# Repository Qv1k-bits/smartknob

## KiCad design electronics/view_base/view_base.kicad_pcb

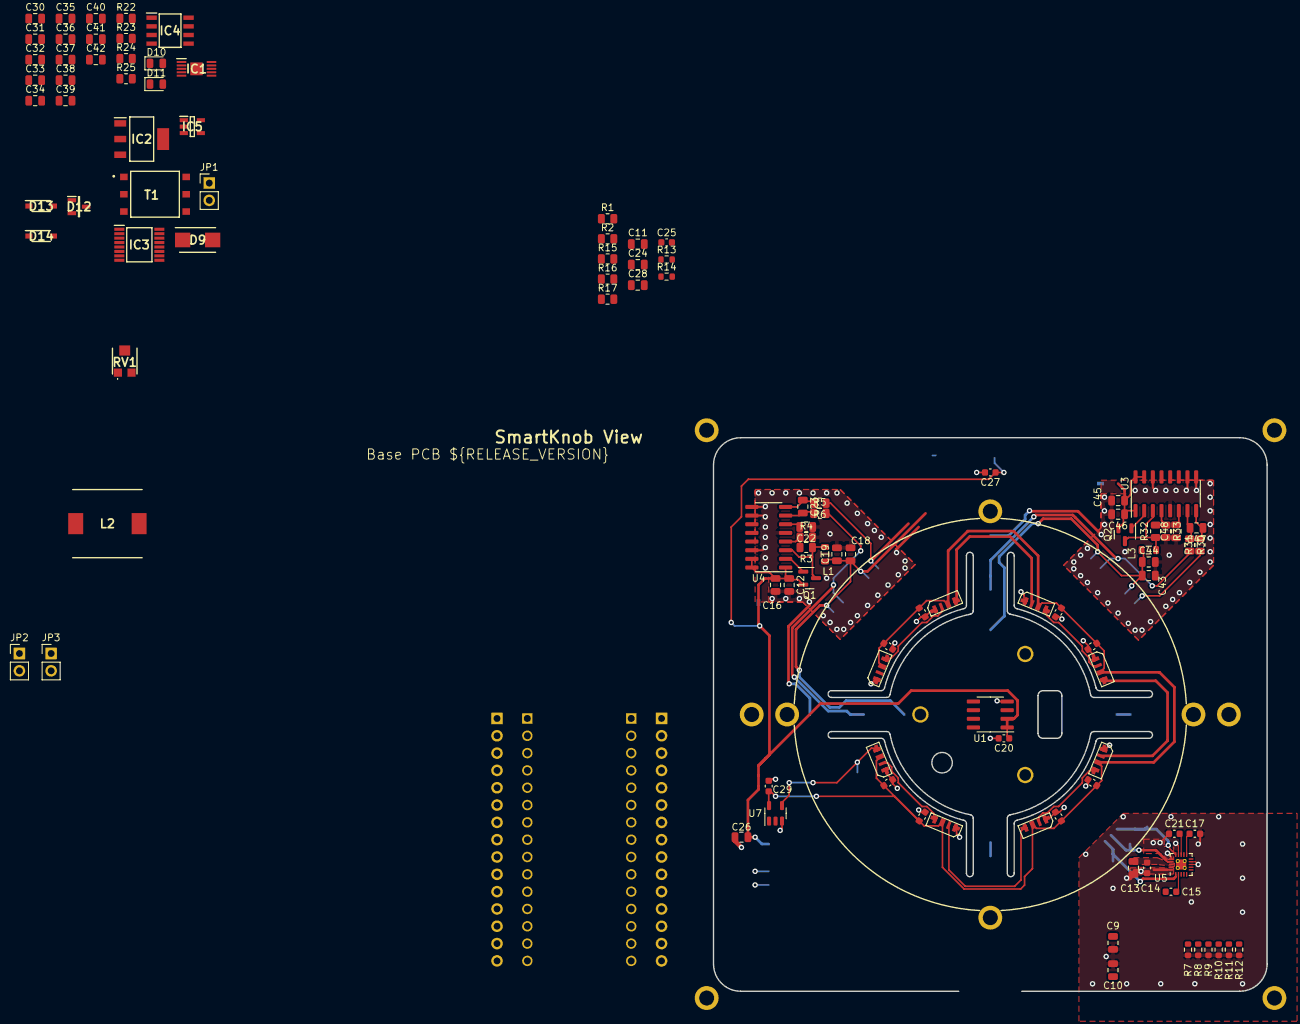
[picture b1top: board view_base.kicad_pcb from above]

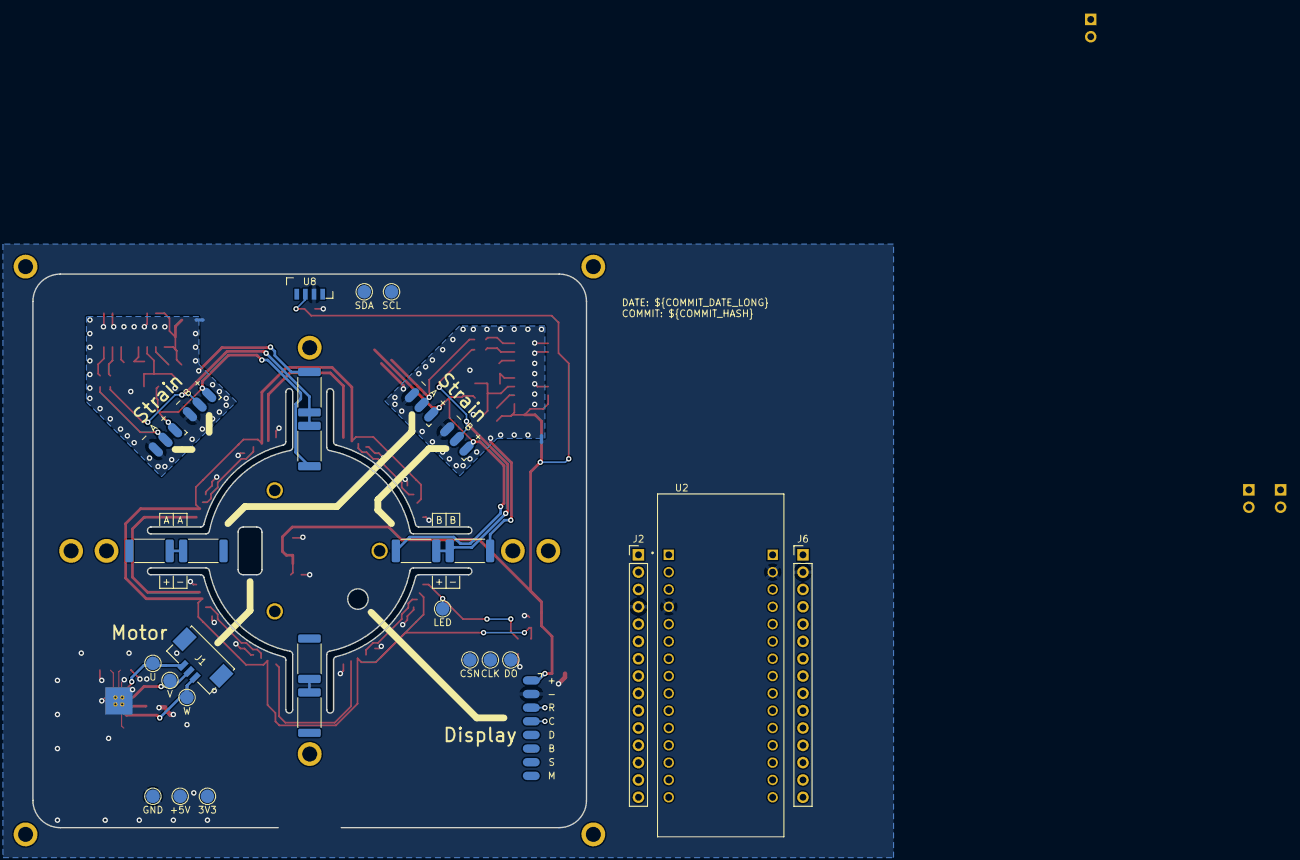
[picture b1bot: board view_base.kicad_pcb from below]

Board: 2 copper layers, 81.2 x 81.2 mm, 158 parts (32 on the bottom side), 91 nets.

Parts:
C1, C2, C3, C4, C5, C6, C7, C8, C14, C15, C17, C20, C21, C25, C27, C29: 0.1uF; C_0603_1608Metric
C9: 10uF/50V; C_0805_2012Metric
C10, C30, C32, C38, C41: 100nF; C_0805_2012Metric
C11, C31: 10nF; C_0805_2012Metric
C12, C19, C22, C23, C44, C46, C47, C48: 0.1uF; C_0805_2012Metric
C13: 22uF; C_0805_2012Metric
C16, C18, C24, C26, C43, C45: 10uF; C_0805_2012Metric
C28, C33: 3nF; C_0805_2012Metric
C34: 8.2pF; C_0805_2012Metric
C35, C36, C37: 47uF; C_0805_2012Metric
C39: 4.7u; C_0805_2012Metric
C40, C42: 50/1uF; C_0805_2012Metric
D1, D2, D3, D4, D5, D6, D7, D8: SK6812SIDE-A; SK6812-SIDE-A
D9: B360B-13-F; DIOM5336X250N
D10: Green; D_0805_2012Metric
D11: Red; D_0805_2012Metric
D12: SP712-02HTG; SOT95P237X115-3N
D13, D14: MBR0520L-TP; SOD3716X135N
H1, H2, H3: MotorHole; MountingHole_M1.6
H4, H5, H6, H7, H10, H11, H12, H13: MountHole; MountingHole_2.2mm_M2_ISO7380_Pad_NonVirtual
H8, H9: AlignmentHole; MountingHole_2.2mm_M2_ISO7380_Pad_NonVirtual
IC1: TPS54240DGQR; SOP50P490X110-11N
IC2: MCP1826ST-3302E_DB; SOT230P700X180-4N
IC3: TCA9534APWR; SOP65P640X120-16N
IC4: ISO1044BDR; SOIC127P600X175-8N
IC5: SN6501QDBVRQ1; SOT95P280X145-5N
J1: BLDC; 532610371
J2, J6: Conn_01x15; PinHeader_1x15_P2.54mm_Vertical
J3: LCD; SolderPads_2mm_8
J4, J7: A; SolderPads_2mm_3_STRAIN
J5, J8: B; SolderPads_2mm_3_STRAIN
JP1: PinHeader_1x02_P2.54mm_Vertical
JP2, JP3: Jumper_2_Open; PinHeader_1x02_P2.54mm_Vertical
L1, L3: 3.3uH; L_0805_2012Metric
L2: 10uH; INDPM102100X400N
NT1, NT2: NetTie_2; NetTie-2_SMD_Pad0.5mm
Q1, Q2: MMBT4403; SOT-23
R1: 105k; R_0805_2012Metric
R2: 12k1; R_0805_2012Metric
R3, R16, R23, R32: 10k; R_0805_2012Metric
R4, R33: 8.2k; R_0805_2012Metric
R5, R6, R30, R31: 100; R_0805_2012Metric
R7, R8, R9, R10, R11, R12: 10k; R_0603_1608Metric
R13, R14: 2.2k; R_0603_1608Metric
R15: 249k; R_0805_2012Metric
R17: 36k5; R_0805_2012Metric
R18, R19, R20, R21, R26, R27, R28, R29: 330; R_2512_6332Metric
R22: ~50k; R_0805_2012Metric
R24: 1k; R_0805_2012Metric
R25: 120; R_0805_2012Metric
RV1: 5k; TC33X2503E
T1: 760390014; 760390015
TP1: 3V3; TestPoint_Pad_D2.0mm_ValueSilk
TP2: GND; TestPoint_Pad_D2.0mm_ValueSilk
TP3: +5V; TestPoint_Pad_D2.0mm_ValueSilk
TP4: SDA; TestPoint_Pad_D2.0mm_ValueSilk
TP5: SCL; TestPoint_Pad_D2.0mm_ValueSilk
TP6: U; TestPoint_Pad_D2.0mm_ValueSilk
TP7: V; TestPoint_Pad_D2.0mm_ValueSilk
TP8: W; TestPoint_Pad_D2.0mm_ValueSilk
TP9: CSN; TestPoint_Pad_D2.0mm_ValueSilk
TP10: CLK; TestPoint_Pad_D2.0mm_ValueSilk
TP11: DO; TestPoint_Pad_D2.0mm_ValueSilk
TP12: LED; TestPoint_Pad_D2.0mm_ValueSilk
U1: MT6701-CT; SOIC-8_3.9x4.9mm_P1.27mm
U2: NUCLEO-L432KC; MODULE_NUCLEO-L432KC
U3, U4: HX711; SOIC-16_3.9x9.9mm_P1.27mm
U5: TMC6300; QFN-20-1EP_3x3mm_P0.4mm_EP1.65x1.65mm_ThermalVias_LargerVia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
U7: SN74LV1T34DBV; SOT-23-5
U8: VEML7700; VEML7700-TOP
Z5: dummy_keepouts; ViewKeepouts3d
Z6, Z7, Z8: RotorScrew (BOM-only); bom_only_no_pin
Z9: WatchGlass39.5mm; bom_only_no_pin
Z10: BLDCMotor; bom_only_no_pin

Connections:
+3V3: C12.1, C16.1, C17.1, C20.1, C26.1, C27.1, C30.1, C31.1, C38.1, C39.1, C45.1, C46.1, IC2.3 (VOUT), IC3.16 (VCC), IC4.1 (VCC1), J3.1, J6.14, Q1.2 (E), Q2.2 (E), R13.1, R14.1, TP1.1, U1.1 (VDD), U1.2 (MODE), U2.CN4_14 (+3V3), U3.1 (VSUP), U3.15 (RATE), U3.16 (DVDD), U4.1 (VSUP), U4.15 (RATE), U4.16 (DVDD), U5.11 (VIO/~STDBY), U8.2 (VDD)
+5V: C1.1, C2.1, C3.1, C4.1, C5.1, C6.1, C7.1, C8.1, C10.1, C11.1, C13.1, C14.1, C15.1, C24.1, C25.1, C29.1, C35.1, C36.1, C37.1, C40.1, D1.2 (VDD), D2.2 (VDD), D3.2 (VDD), D4.2 (VDD), D5.2 (VDD), D6.2 (VDD), D7.2 (VDD), D8.2 (VDD), D11.1 (K), IC2.1 (VIN), IC5.2 (VCC), J6.4, JP3.1 (A), JP3.2 (B), L2.2, RV1.2, T1.2, TP3.1, U2.CN4_4 (+5V), U5.18 (VS), U7.5 (VCC)
+5VP: C41.1, C42.1, D13.1 (K), D14.1 (K), IC4.8 (VCC2)
+12V: C9.1, IC1.2 (VIN), JP2.2 (B), R1.1, R16.1
/AREF: J6.13, U2.CN4_13 (AREF)
/CANH: D12.2 (K_2), IC4.6 (CANH), JP1.1 (A)
/CANL: D12.1 (K_1), IC4.5 (CANL), R25.2
/LED_DATA_5V: D1.1 (DIN), TP12.1, U7.4 (Y)
/MAG_CSN: TP9.1, U1.8 (Z/W/CSN)
/NRST_CN3: J2.3, U2.CN3_3 (NRST_CN3)
/NRST_CN4: J6.3, U2.CN4_3 (NRST_CN4)
/PA0: J6.12, U2.CN4_12 (PA0)
/PA1: J6.11, U2.CN4_11 (PA1)
/PA2: J6.5, U2.CN4_5 (PA2)
/PA3: J6.10, U2.CN4_10 (PA3)
/PA4: J6.9, U2.CN4_9 (PA4)
/PA5: J6.8, U2.CN4_8 (PA5)
/PA6: J6.7, U2.CN4_7 (PA6)
/PA7: J6.6, U2.CN4_6 (PA7)
/PA8: J2.12, U2.CN3_12 (PA8)
/PA9: IC3.14 (SCL), J2.1, J3.4, R14.2, TP5.1, TP10.1, U1.7 (B/V/SCL/CLK), U2.CN3_1 (PA9), U8.1 (SCL)
/PA10: IC3.15 (SDA), J2.2, J3.5, R13.2, TP4.1, TP11.1, U1.6 (A/U/SDA/DO), U2.CN3_2 (PA10), U8.4 (SDA)
/PB0: J2.6, U2.CN3_6 (PB0)
/PB1: J2.9, U2.CN3_9 (PB1)
/PB3: J6.15, U2.CN4_15 (PB3)
/PB4: J2.15, U2.CN3_15 (PB4)
/PB5: J2.14, U2.CN3_14 (PB5)
/PB6: J2.8, U2.CN3_8 (PB6)
/PB7: J2.7, U2.CN3_7 (PB7)
/PC14: J2.10, U2.CN3_10 (PC14)
/PC15: J2.11, U2.CN3_11 (PC15)
/Strain_sensor_1/STRAIN_E+: C43.1, C44.1, J7.1, J8.1, L3.2, R26.1, R28.2
/Strain_sensor_1/STRAIN_S+: J7.2, R26.2, R27.1, R31.1
/Strain_sensor_1/STRAIN_S-: J8.2, R28.1, R29.2, R30.2
/Strain_sensor_2/STRAIN_E+: C18.1, C19.1, J4.1, J5.1, L1.2, R18.1, R20.2
/Strain_sensor_2/STRAIN_S+: J4.2, R6.1, R18.2, R19.1
/Strain_sensor_2/STRAIN_S-: J5.2, R5.2, R20.1, R21.2
/TMC_DIAG: IC3.4 (P0), U5.12 (DIAG)
/TMC_UH: IC3.5 (P1), R7.1, U5.3 (UH)
/TMC_UL: IC3.6 (P2), R10.1, U5.6 (UL)
/TMC_VH: IC3.7 (P3), R8.1, U5.4 (VH)
/TMC_VL: IC3.9 (P4), R12.1, U5.10 (VL)
/TMC_WH: IC3.10 (P5), R9.1, U5.5 (WH)
/TMC_WL: IC3.11 (P6), R11.1, U5.7 (WL)
/VIN: J6.1, JP2.1 (A), U2.CN4_1 (VIN)
/stm32.CAN_RD: IC4.3 (RXD), J2.13, U2.CN3_13 (PA11)
/stm32.CAN_TD: IC4.2 (TXD), J2.5, U2.CN3_5 (PA12)
GND: C1.2, C2.2, C3.2, C4.2, C5.2, C6.2, C7.2, C8.2, C9.2, C10.2, C11.2, C13.2, C14.2, C17.2, C20.2, C21.2, C24.2, C25.2, C26.2, C27.2, C28.2, C29.2, C30.2, C31.2, C33.2, C34.2, C35.2, C36.2, C37.2, C38.2, C39.2, C40.2, D1.4 (VSS), D2.4 (VSS), D3.4 (VSS), D4.4 (VSS), D5.4 (VSS), D6.4 (VSS), D7.4 (VSS), D8.4 (VSS), D9.2 (A), IC1.9 (GND), IC1.11 (EP), IC2.2 (GND_1), IC2.4 (GND_2), IC3.1 (A0), IC3.2 (A1), IC3.3 (A2), IC3.8 (GND), IC4.4 (GND1), IC5.4 (GND_1), IC5.5 (GND_2), J2.4, J3.2, J6.2, NT1.2, NT2.2, R2.2, R7.2, R8.2, R9.2, R10.2, R11.2, R12.2, R15.2, R23.2, R24.2, TP2.1, U1.4 (GND), U2.CN3_4 (GND_CN3), U2.CN4_2 (GND_CN4), U5.8 (GND), U5.9 (GND), U5.14 (GND), U5.16 (BRUV), U5.20 (BRW), U5.PAD, U7.3 (GND), U8.3 (GND)
GNDA: C12.2, C16.2, C18.2, C19.2, C22.1, C43.2, C44.2, C45.2, C46.2, C48.1, J4.3, J5.3, J7.3, J8.3, NT1.1, NT2.1, R4.2, R19.2, R21.1, R27.2, R29.1, R33.2, U3.5 (AGND), U3.9 (INB-), U3.10 (INB+), U3.14 (XI), U4.5 (AGND), U4.9 (INB-), U4.10 (INB+), U4.14 (XI)
GNDS: C41.2, C42.2, D12.3 (COMMON), IC4.7 (GND2), T1.5
unnamed: C33.1, R17.1
unnamed: D1.3 (DOUT), D2.1 (DIN)
unnamed: D2.3 (DOUT), D3.1 (DIN)
unnamed: D3.3 (DOUT), D4.1 (DIN)
unnamed: D4.3 (DOUT), D5.1 (DIN)
unnamed: D5.3 (DOUT), D6.1 (DIN)
unnamed: D6.3 (DOUT), D7.1 (DIN)
unnamed: D7.3 (DOUT), D8.1 (DIN)
unnamed: C32.1, D9.1 (K), IC1.10 (PH), L2.1
unnamed: D10.2 (A), R16.2
unnamed: D10.1 (K), IC1.6 (PWRGD)
unnamed: D11.2 (A), R24.1
unnamed: D13.2 (A), T1.6
unnamed: D14.2 (A), T1.4
unnamed: C32.2, IC1.1 (BOOT)
unnamed: C34.1, IC1.8 (COMP), R17.2
unnamed: IC1.3 (EN), R1.2, R2.1
unnamed: IC1.5 (RT/CLK), R15.1
unnamed: C28.1, IC1.4 (SS/TR)
unnamed: IC1.7 (VSENSE), R22.2, R23.1
unnamed: IC5.1 (D1), T1.3
unnamed: IC5.3 (D2), T1.1
unnamed: J1.1, TP8.1, U5.1 (W)
unnamed: J1.2, TP7.1, U5.17 (V)
unnamed: J1.3, TP6.1, U5.15 (U)
unnamed: JP1.2 (B), R25.1
unnamed: Q1.1 (B), U4.2 (BASE)
unnamed: L1.1, Q1.3 (C), R3.1, U4.3 (AVDD)
unnamed: Q2.1 (B), U3.2 (BASE)
unnamed: L3.1, Q2.3 (C), R32.1, U3.3 (AVDD)
unnamed: R22.1, RV1.1
unnamed: C47.1, R31.2, U3.8 (INA+)
unnamed: C47.2, R30.1, U3.7 (INA-)
unnamed: C48.2, U3.6 (VBG)
unnamed: R32.2, R33.1, U3.4 (VFB)
unnamed: C23.1, R6.2, U4.8 (INA+)
unnamed: C23.2, R5.1, U4.7 (INA-)
unnamed: C22.2, U4.6 (VBG)
unnamed: R3.2, R4.1, U4.4 (VFB)
unnamed: C21.1, U5.13 (1V8OUT)
unnamed: C15.2, U5.2 (VCP)

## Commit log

2024-01-25 more

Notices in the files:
parts and their libraries:
Copyright 2021 Accelerated Designs. All rights reserved.
